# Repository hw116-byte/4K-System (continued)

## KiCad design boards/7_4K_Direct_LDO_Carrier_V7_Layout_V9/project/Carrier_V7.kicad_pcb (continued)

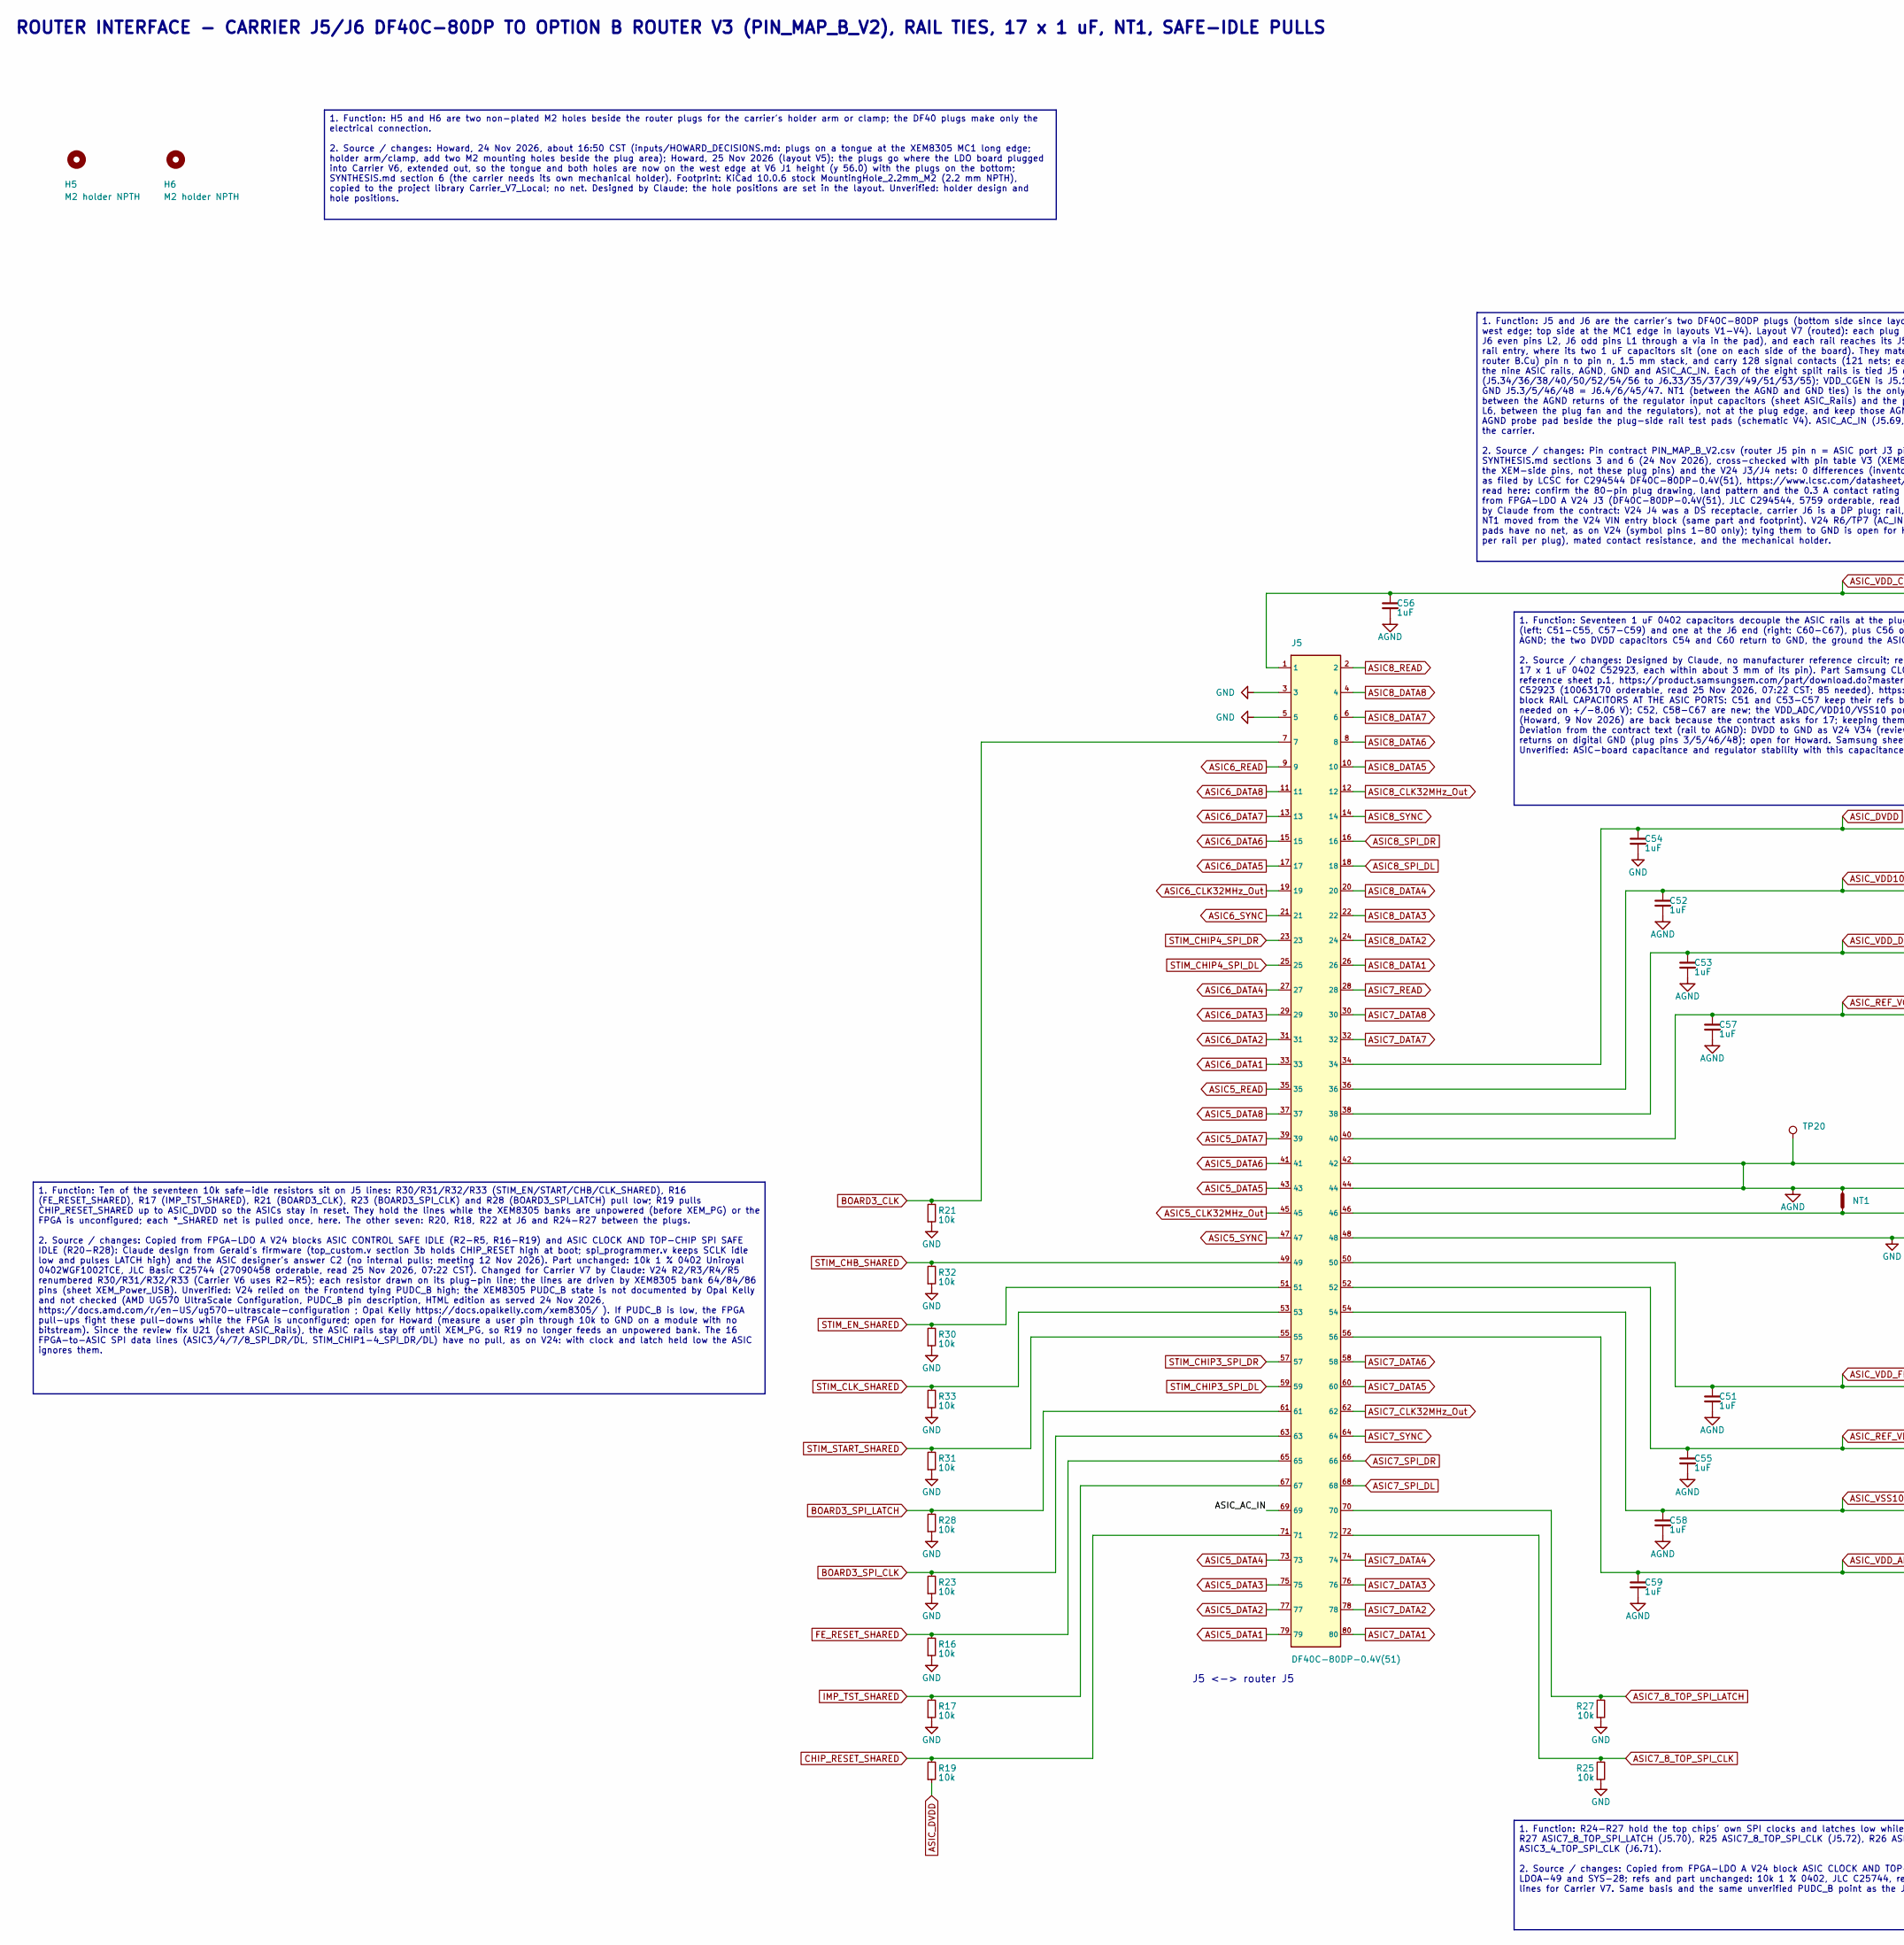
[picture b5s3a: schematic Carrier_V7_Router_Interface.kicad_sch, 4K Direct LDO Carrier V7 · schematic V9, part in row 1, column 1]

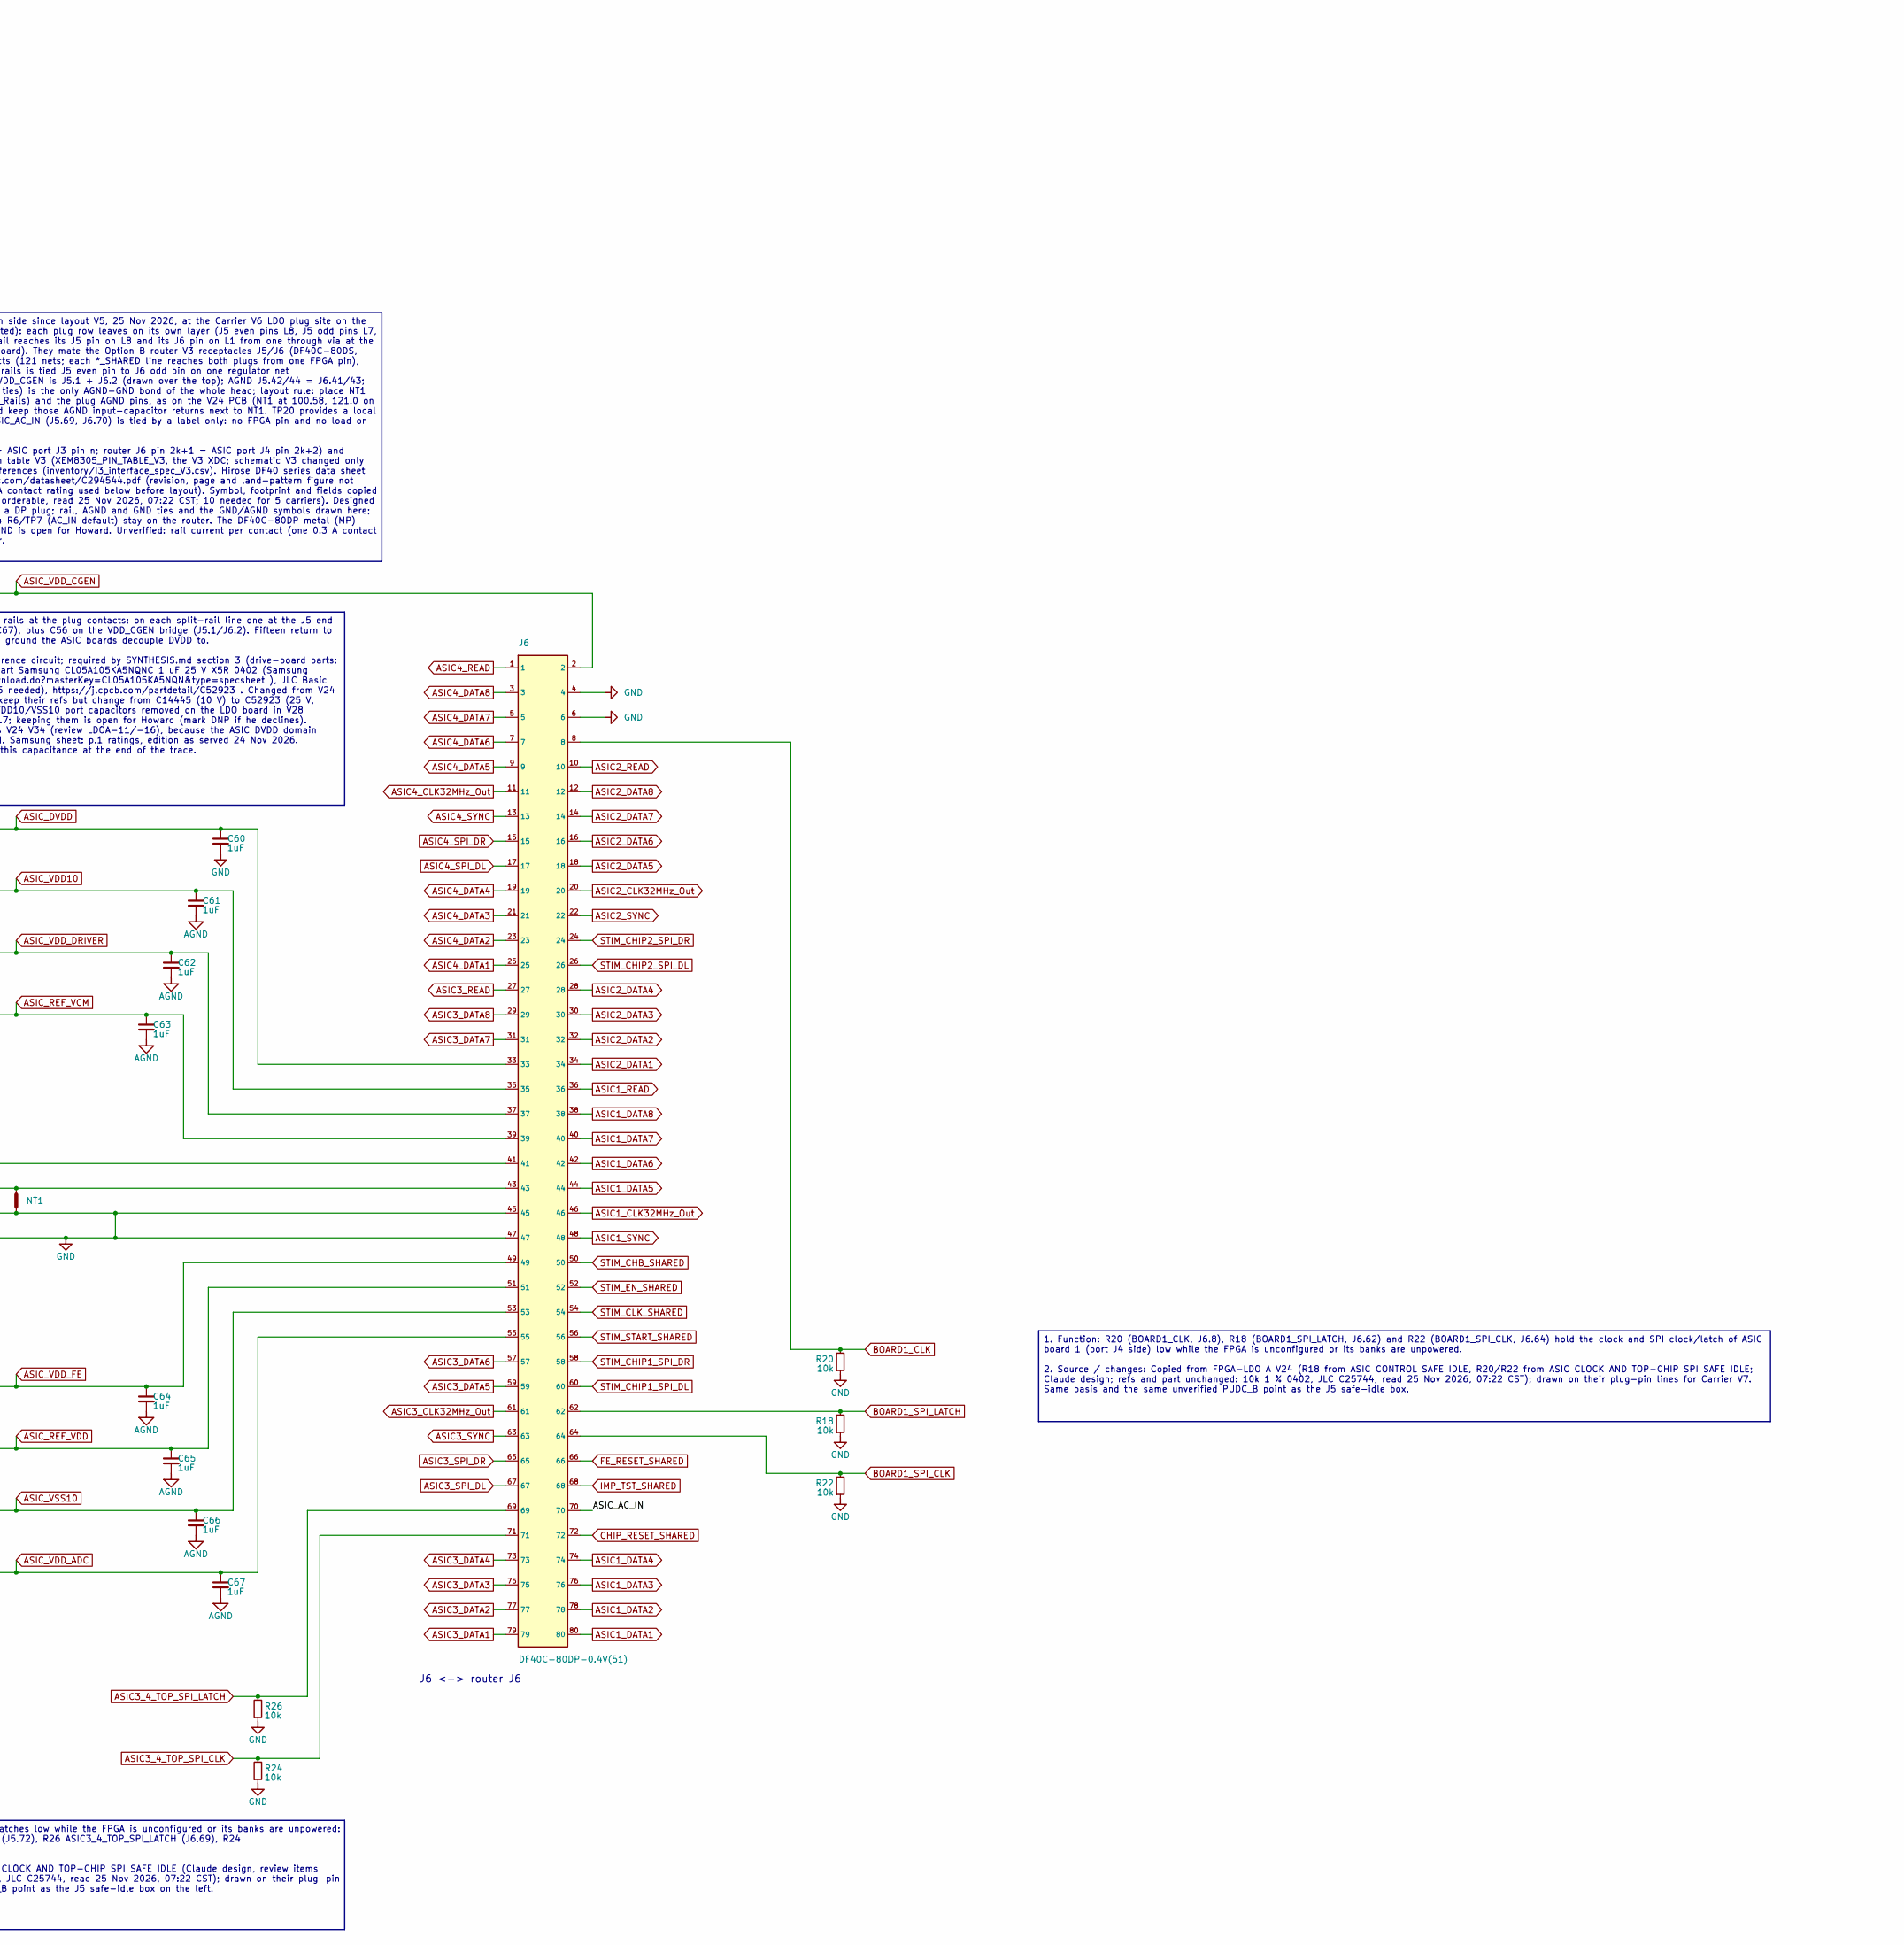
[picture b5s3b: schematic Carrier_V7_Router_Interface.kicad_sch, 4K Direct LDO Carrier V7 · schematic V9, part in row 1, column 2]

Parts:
C51, C52, C53, C54, C55, C56, C57, C58, C59, C60, C61, C62, C63, C64, C65, C66, C67: 1uF; C_0402_1005Metric; Voltage 25V; MPN Samsung CL05A105KA5NQNC (1 uF 25 V X5R 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; LCSC C52923
H5, H6: M2 holder NPTH; MountingHole_2.2mm_M2
J5, J6: DF40C-80DP-0.4V(51); Hirose_DF40C-80DP-0.4V_2x40-1MP_P0.4mm; MPN DF40C-80DP-0.4V(51); LCSC C294544
NT1: NetTie_2; NetTie-2_SMD_Pad0.5mm
R16, R17, R18, R19, R30, R31, R32, R33: 10k; R_0402_1005Metric; Tolerance 1%; LCSC C25744
R20, R21, R22, R23, R24, R25, R26, R27, R28: 10k; R_0402_1005Metric; Tolerance 1%; MPN Uniroyal 0402WGF1002TCE (10k 1% 0402); LCSC C25744
TP20: AGND; TestPoint_Pad_D1.0mm_Compact

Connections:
/Router_Interface/ASIC_AC_IN: J5.69, J6.70
AGND: C51.2, C52.2, C53.2, C55.2, C56.2, C57.2, C58.2, C59.2, C61.2, C62.2, C63.2, C64.2, C65.2, C66.2, C67.2, J5.42, J5.44, J6.41, J6.43, NT1.2, TP20.1; also elsewhere on the board
ASIC1_CLK32MHz_Out: J6.46; also elsewhere on the board
ASIC1_DATA1: J6.80; also elsewhere on the board
ASIC1_DATA2: J6.78; also elsewhere on the board
ASIC1_DATA3: J6.76; also elsewhere on the board
ASIC1_DATA4: J6.74; also elsewhere on the board
ASIC1_DATA5: J6.44; also elsewhere on the board
ASIC1_DATA6: J6.42; also elsewhere on the board
ASIC1_DATA7: J6.40; also elsewhere on the board
ASIC1_DATA8: J6.38; also elsewhere on the board
ASIC1_READ: J6.36; also elsewhere on the board
ASIC1_SYNC: J6.48; also elsewhere on the board
ASIC2_CLK32MHz_Out: J6.20; also elsewhere on the board
ASIC2_DATA1: J6.34; also elsewhere on the board
ASIC2_DATA2: J6.32; also elsewhere on the board
ASIC2_DATA3: J6.30; also elsewhere on the board
ASIC2_DATA4: J6.28; also elsewhere on the board
ASIC2_DATA5: J6.18; also elsewhere on the board
ASIC2_DATA6: J6.16; also elsewhere on the board
ASIC2_DATA7: J6.14; also elsewhere on the board
ASIC2_DATA8: J6.12; also elsewhere on the board
ASIC2_READ: J6.10; also elsewhere on the board
ASIC2_SYNC: J6.22; also elsewhere on the board
ASIC3_4_TOP_SPI_CLK: J6.71, R24.1; also elsewhere on the board
ASIC3_4_TOP_SPI_LATCH: J6.69, R26.1; also elsewhere on the board
ASIC3_CLK32MHz_Out: J6.61; also elsewhere on the board
ASIC3_DATA1: J6.79; also elsewhere on the board
ASIC3_DATA2: J6.77; also elsewhere on the board
ASIC3_DATA3: J6.75; also elsewhere on the board
ASIC3_DATA4: J6.73; also elsewhere on the board
ASIC3_DATA5: J6.59; also elsewhere on the board
ASIC3_DATA6: J6.57; also elsewhere on the board
ASIC3_DATA7: J6.31; also elsewhere on the board
ASIC3_DATA8: J6.29; also elsewhere on the board
ASIC3_READ: J6.27; also elsewhere on the board
ASIC3_SPI_DL: J6.67; also elsewhere on the board
ASIC3_SPI_DR: J6.65; also elsewhere on the board
ASIC3_SYNC: J6.63; also elsewhere on the board
ASIC4_CLK32MHz_Out: J6.11; also elsewhere on the board
ASIC4_DATA1: J6.25; also elsewhere on the board
ASIC4_DATA2: J6.23; also elsewhere on the board
ASIC4_DATA3: J6.21; also elsewhere on the board
ASIC4_DATA4: J6.19; also elsewhere on the board
ASIC4_DATA5: J6.9; also elsewhere on the board
ASIC4_DATA6: J6.7; also elsewhere on the board
ASIC4_DATA7: J6.5; also elsewhere on the board
ASIC4_DATA8: J6.3; also elsewhere on the board
ASIC4_READ: J6.1; also elsewhere on the board
ASIC4_SPI_DL: J6.17; also elsewhere on the board
ASIC4_SPI_DR: J6.15; also elsewhere on the board
ASIC4_SYNC: J6.13; also elsewhere on the board
ASIC5_CLK32MHz_Out: J5.45; also elsewhere on the board
ASIC5_DATA1: J5.79; also elsewhere on the board
ASIC5_DATA2: J5.77; also elsewhere on the board
ASIC5_DATA3: J5.75; also elsewhere on the board
ASIC5_DATA4: J5.73; also elsewhere on the board
ASIC5_DATA5: J5.43; also elsewhere on the board
ASIC5_DATA6: J5.41; also elsewhere on the board
ASIC5_DATA7: J5.39; also elsewhere on the board
ASIC5_DATA8: J5.37; also elsewhere on the board
ASIC5_READ: J5.35; also elsewhere on the board
ASIC5_SYNC: J5.47; also elsewhere on the board
ASIC6_CLK32MHz_Out: J5.19; also elsewhere on the board
ASIC6_DATA1: J5.33; also elsewhere on the board
ASIC6_DATA2: J5.31; also elsewhere on the board
ASIC6_DATA3: J5.29; also elsewhere on the board
ASIC6_DATA4: J5.27; also elsewhere on the board
ASIC6_DATA5: J5.17; also elsewhere on the board
ASIC6_DATA6: J5.15; also elsewhere on the board
ASIC6_DATA7: J5.13; also elsewhere on the board
ASIC6_DATA8: J5.11; also elsewhere on the board
ASIC6_READ: J5.9; also elsewhere on the board
ASIC6_SYNC: J5.21; also elsewhere on the board
ASIC7_8_TOP_SPI_CLK: J5.72, R25.1; also elsewhere on the board
ASIC7_8_TOP_SPI_LATCH: J5.70, R27.1; also elsewhere on the board
ASIC7_CLK32MHz_Out: J5.62; also elsewhere on the board
ASIC7_DATA1: J5.80; also elsewhere on the board
ASIC7_DATA2: J5.78; also elsewhere on the board
ASIC7_DATA3: J5.76; also elsewhere on the board
ASIC7_DATA4: J5.74; also elsewhere on the board
ASIC7_DATA5: J5.60; also elsewhere on the board
ASIC7_DATA6: J5.58; also elsewhere on the board
ASIC7_DATA7: J5.32; also elsewhere on the board
ASIC7_DATA8: J5.30; also elsewhere on the board
ASIC7_READ: J5.28; also elsewhere on the board
ASIC7_SPI_DL: J5.68; also elsewhere on the board
ASIC7_SPI_DR: J5.66; also elsewhere on the board
ASIC7_SYNC: J5.64; also elsewhere on the board
ASIC8_CLK32MHz_Out: J5.12; also elsewhere on the board
ASIC8_DATA1: J5.26; also elsewhere on the board
ASIC8_DATA2: J5.24; also elsewhere on the board
ASIC8_DATA3: J5.22; also elsewhere on the board
ASIC8_DATA4: J5.20; also elsewhere on the board
ASIC8_DATA5: J5.10; also elsewhere on the board
ASIC8_DATA6: J5.8; also elsewhere on the board
ASIC8_DATA7: J5.6; also elsewhere on the board
ASIC8_DATA8: J5.4; also elsewhere on the board
ASIC8_READ: J5.2; also elsewhere on the board
ASIC8_SPI_DL: J5.18; also elsewhere on the board
ASIC8_SPI_DR: J5.16; also elsewhere on the board
ASIC8_SYNC: J5.14; also elsewhere on the board
ASIC_DVDD: C54.1, C60.1, J5.34, J6.33, R19.2; also elsewhere on the board
ASIC_REF_VCM: C57.1, C63.1, J5.40, J6.39; also elsewhere on the board
ASIC_REF_VDD: C55.1, C65.1, J5.52, J6.51; also elsewhere on the board
ASIC_VDD10: C52.1, C61.1, J5.36, J6.35; also elsewhere on the board
ASIC_VDD_ADC: C59.1, C67.1, J5.56, J6.55; also elsewhere on the board
ASIC_VDD_CGEN: C56.1, J5.1, J6.2; also elsewhere on the board
ASIC_VDD_DRIVER: C53.1, C62.1, J5.38, J6.37; also elsewhere on the board
ASIC_VDD_FE: C51.1, C64.1, J5.50, J6.49; also elsewhere on the board
ASIC_VSS10: C58.1, C66.1, J5.54, J6.53; also elsewhere on the board
BOARD1_CLK: J6.8, R20.1; also elsewhere on the board
BOARD1_SPI_CLK: J6.64, R22.1; also elsewhere on the board
BOARD1_SPI_LATCH: J6.62, R18.1; also elsewhere on the board
BOARD3_CLK: J5.7, R21.1; also elsewhere on the board
BOARD3_SPI_CLK: J5.63, R23.1; also elsewhere on the board
BOARD3_SPI_LATCH: J5.61, R28.1; also elsewhere on the board
CHIP_RESET_SHARED: J5.71, J6.72, R19.1; also elsewhere on the board
FE_RESET_SHARED: J5.65, J6.66, R16.1; also elsewhere on the board
GND: C54.2, C60.2, J5.3, J5.5, J5.46, J5.48, J6.4, J6.6, J6.45, J6.47, NT1.1, R16.2, R17.2, R18.2, R20.2, R21.2, R22.2, R23.2, R24.2, R25.2, R26.2, R27.2, R28.2, R30.2, R31.2, R32.2, R33.2; also elsewhere on the board
IMP_TST_SHARED: J5.67, J6.68, R17.1; also elsewhere on the board
STIM_CHB_SHARED: J5.49, J6.50, R32.1; also elsewhere on the board
STIM_CHIP1_SPI_DL: J6.60; also elsewhere on the board
STIM_CHIP1_SPI_DR: J6.58; also elsewhere on the board
STIM_CHIP2_SPI_DL: J6.26; also elsewhere on the board
STIM_CHIP2_SPI_DR: J6.24; also elsewhere on the board
STIM_CHIP3_SPI_DL: J5.59; also elsewhere on the board
STIM_CHIP3_SPI_DR: J5.57; also elsewhere on the board
STIM_CHIP4_SPI_DL: J5.25; also elsewhere on the board
STIM_CHIP4_SPI_DR: J5.23; also elsewhere on the board
STIM_CLK_SHARED: J5.53, J6.54, R33.1; also elsewhere on the board
STIM_EN_SHARED: J5.51, J6.52, R30.1; also elsewhere on the board
STIM_START_SHARED: J5.55, J6.56, R31.1; also elsewhere on the board

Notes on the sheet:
1. Function: J5 and J6 are the carrier's two DF40C-80DP plugs (bottom side since layout V5, 25 Nov 2026, at the Carrier V6 LDO plug site on the west edge; top side at the MC1 edge in layouts V1-V4). Layout V7 (routed): each plug row leaves on its own layer (J5 even pins L8, J5 odd pins L7, J6 even 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
1. Function: Seventeen 1 uF 0402 capacitors decouple the ASIC rails at the plug contacts: on each split-rail line one at the J5 end (left: C51-C55, C57-C59) and one at the J6 end (right: C60-C67), plus C56 on the VDD_CGEN bridge (J5.1/J6.2). Fifteen return to AGND; the two DVDD capacitors C54 and C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
1. Function: Ten of the seventeen 10k safe-idle resistors sit on J5 lines: R30/R31/R32/R33 (STIM_EN/START/CHB/CLK_SHARED), R16 (FE_RESET_SHARED), R17 (IMP_TST_SHARED), R21 (BOARD3_CLK), R23 (BOARD3_SPI_CLK) and R28 (BOARD3_SPI_LATCH) pull low; R19 pulls CHIP_RESET_SHARED up to ASIC_DVDD so the ASIC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
1. Function: R24-R27 hold the top chips' own SPI clocks and latches low while the FPGA is unconfigured or its banks are unpowered: R27 ASIC7_8_TOP_SPI_LATCH (J5.70), R25 ASIC7_8_TOP_SPI_CLK (J5.72), R26 ASIC3_4_TOP_SPI_LATCH (J6.69), R24 ASIC3_4_TOP_SPI_CLK (J6.71). 2. Source / changes: Copied from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
1. Function: R20 (BOARD1_CLK, J6.8), R18 (BOARD1_SPI_LATCH, J6.62) and R22 (BOARD1_SPI_CLK, J6.64) hold the clock and SPI clock/latch of ASIC board 1 (port J4 side) low while the FPGA is unconfigured or its banks are unpowered. 2. Source / changes: Copied from FPGA-LDO A V24 (R18 from ASIC CONTROL 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
1. Function: H5 and H6 are two non-plated M2 holes beside the router plugs for the carrier's holder arm or clamp; the DF40 plugs make only the electrical connection. 2. Source / changes: Howard, 24 Nov 2026, about 16:50 CST (inputs/HOWARD_DECISIONS.md: plugs on a tongue at the XEM8305 MC1 long edge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
ROUTER INTERFACE - CARRIER J5/J6 DF40C-80DP TO OPTION B ROUTER V3 (PIN_MAP_B_V2), RAIL TIES, 17 x 1 uF, NT1, SAFE-IDLE PULLS
J5 <-> router J5
J6 <-> router J6

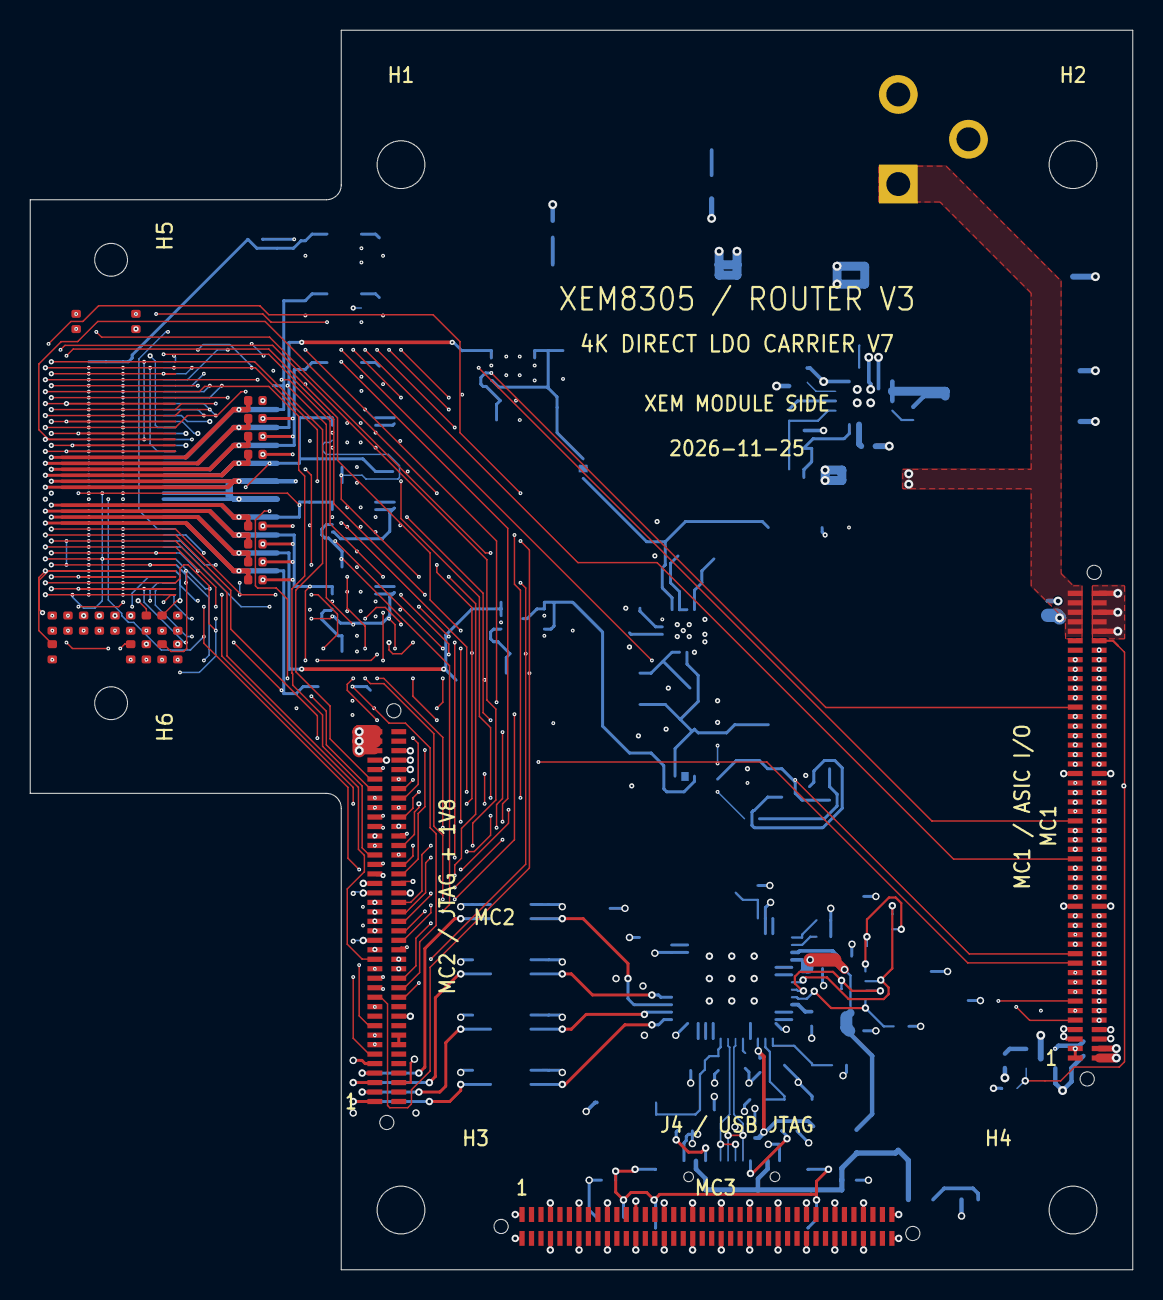
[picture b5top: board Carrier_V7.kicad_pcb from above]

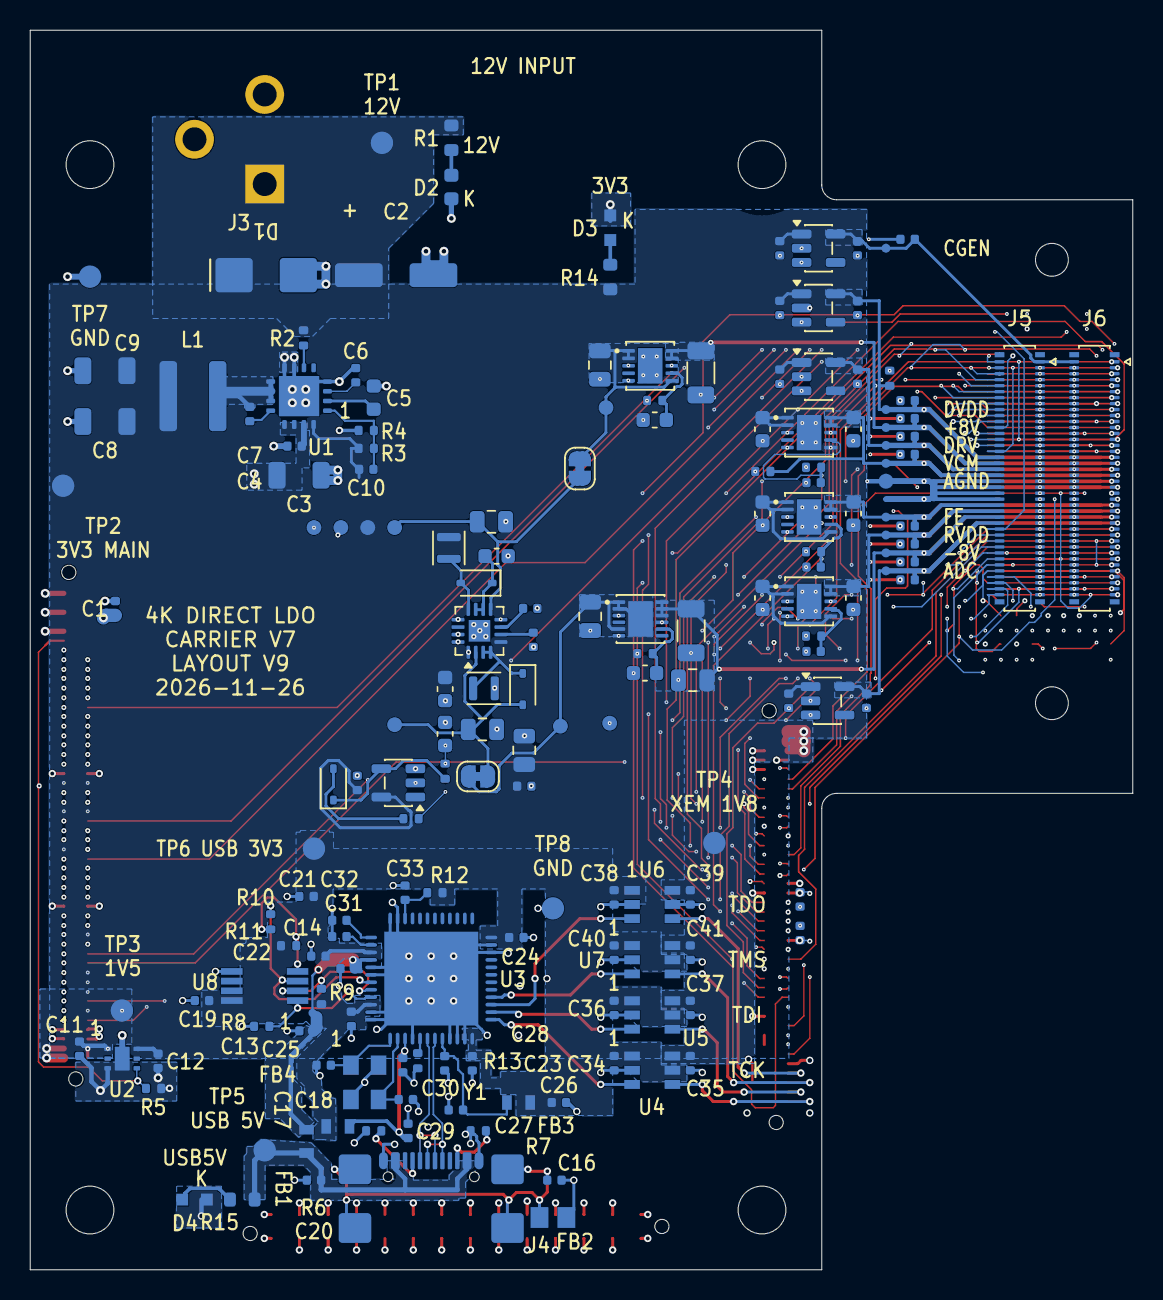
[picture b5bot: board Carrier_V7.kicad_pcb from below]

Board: 8 copper layers, 73.8 x 83.0 mm, 209 parts (176 on the bottom side), 193 nets.
